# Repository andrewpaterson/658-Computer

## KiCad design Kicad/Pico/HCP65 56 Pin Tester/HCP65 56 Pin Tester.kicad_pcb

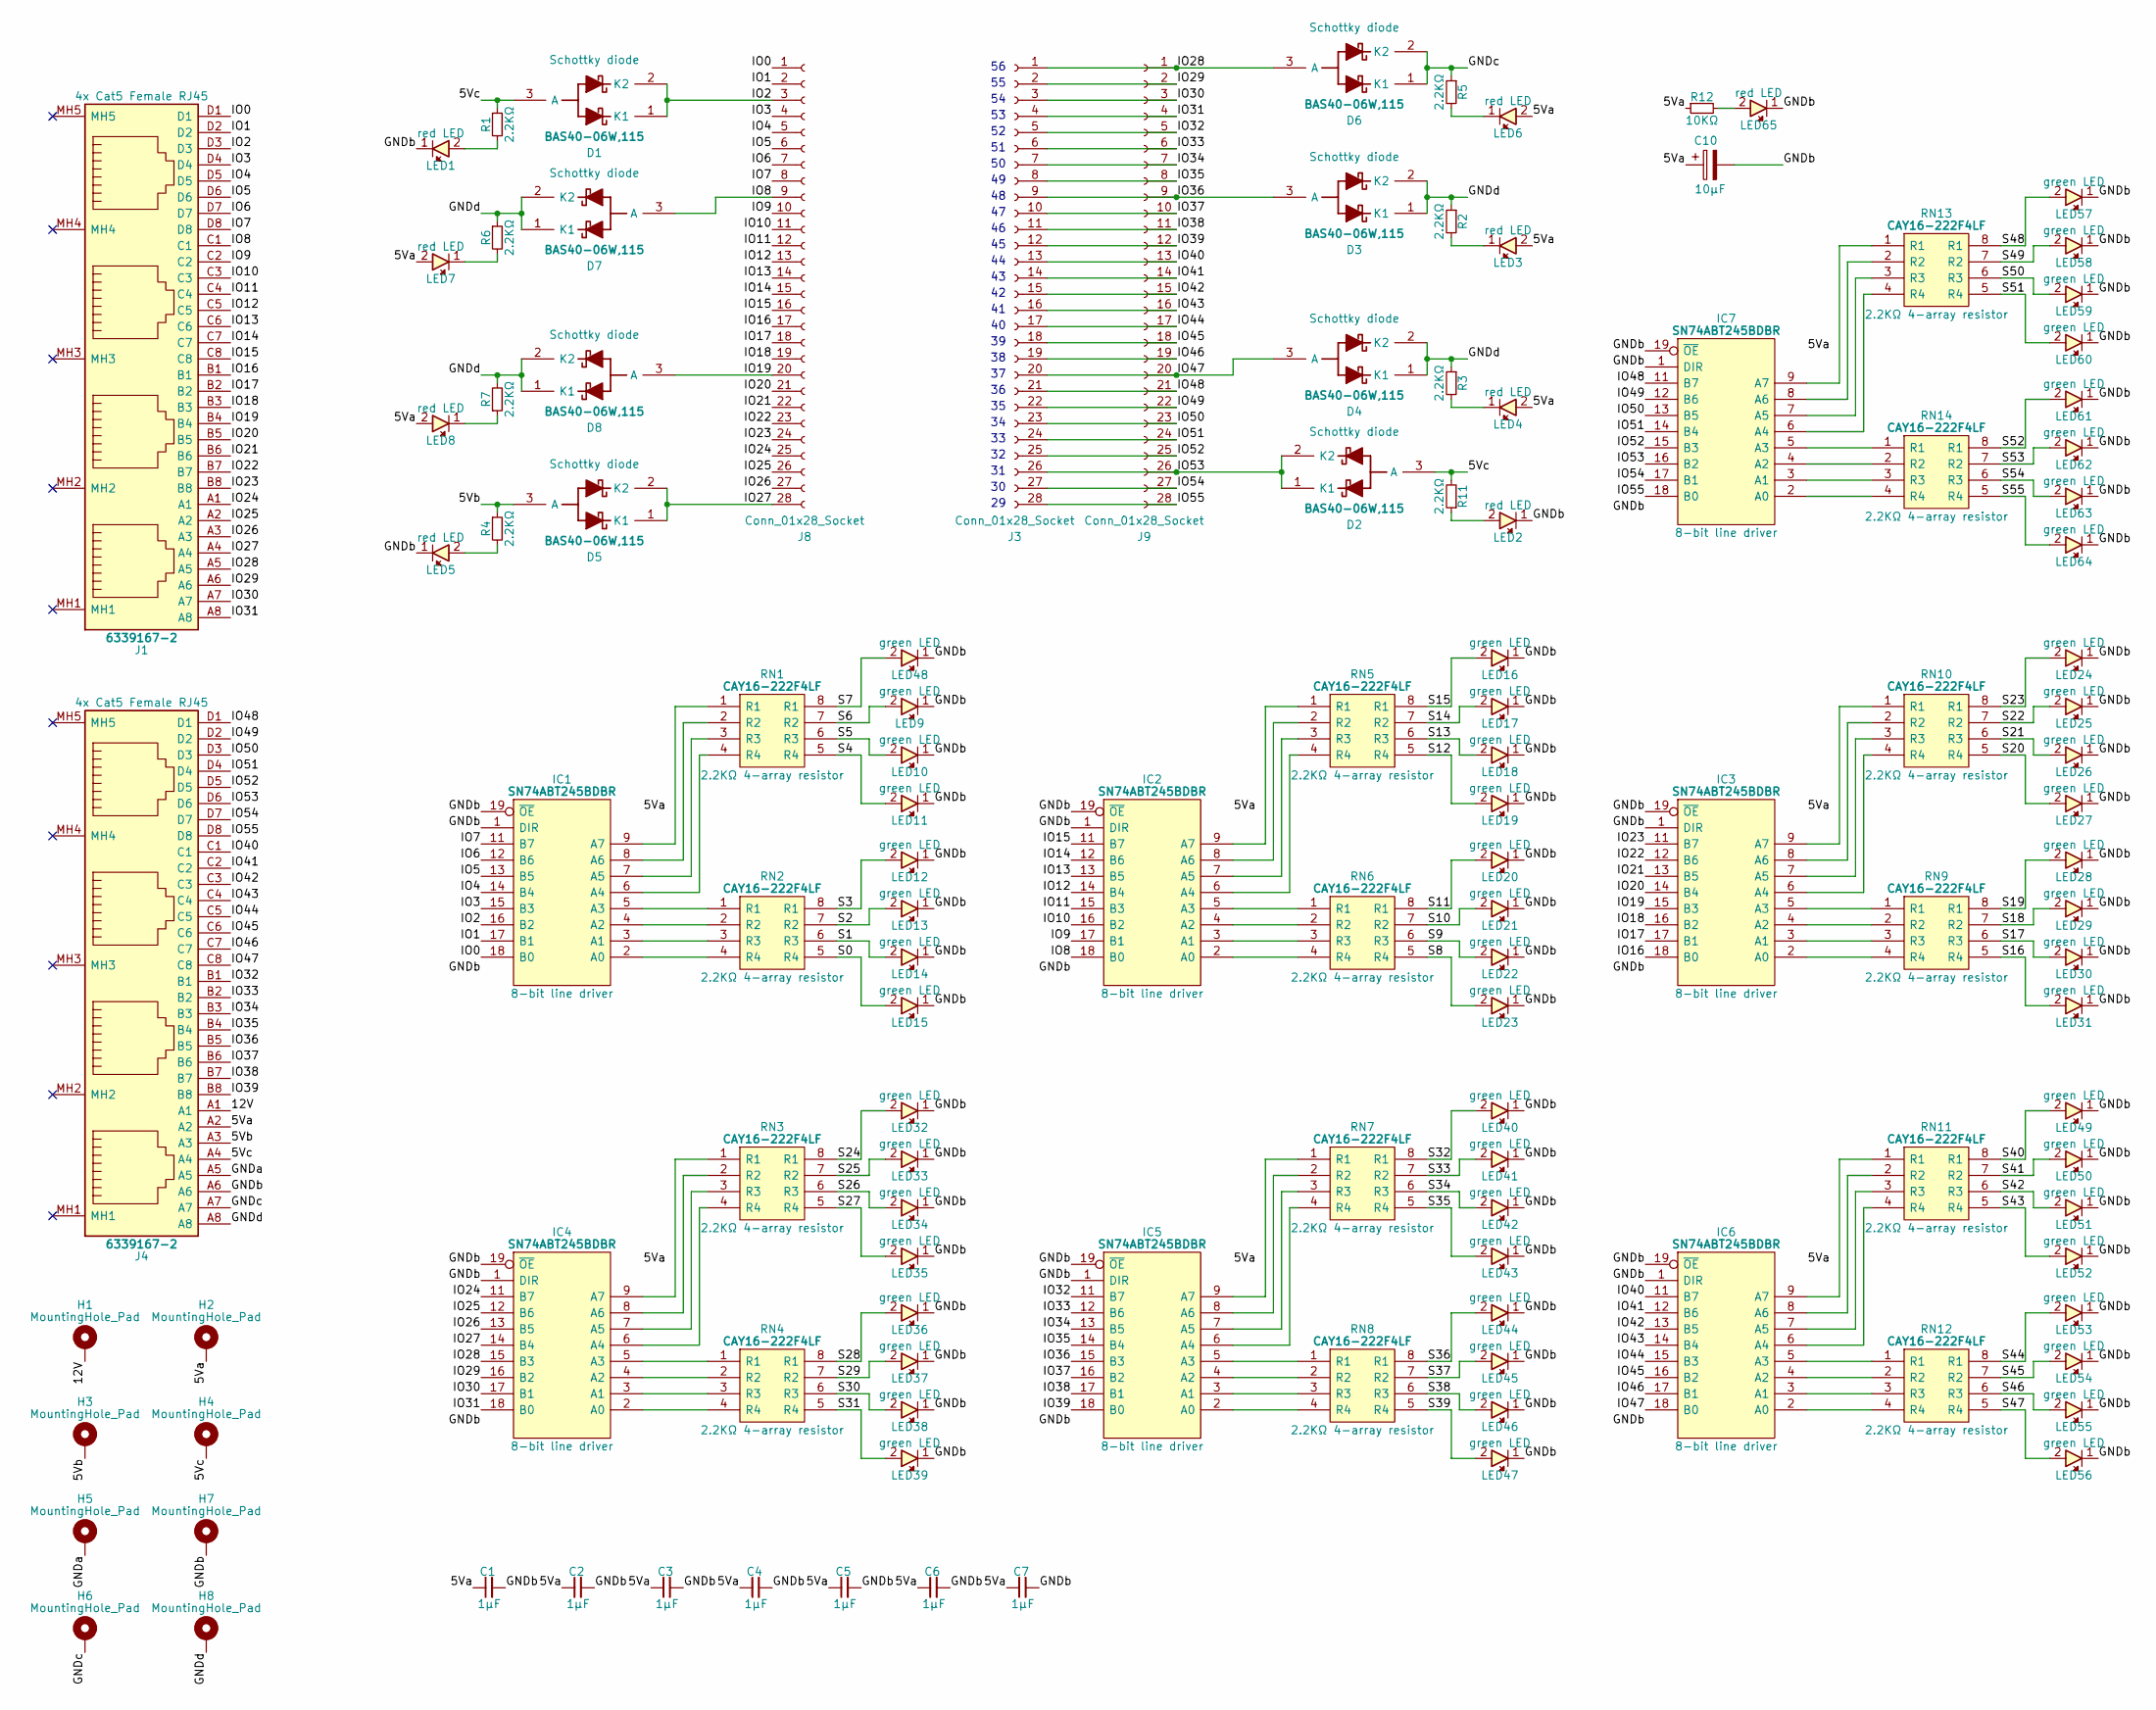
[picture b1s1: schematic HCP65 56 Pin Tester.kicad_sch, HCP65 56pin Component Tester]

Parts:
C1, C2, C3, C4, C5, C6, C7: 1μF; C_0805
C10: 10μF; CP_Radial_D4.0mm_P2.00mm
D1, D2, D3, D4, D5, D6, D7, D8: BAS40-06W,115; SOT65P210X110-3N; Manufacturer_Part_Number BAS40-06W,115; Mouser Part Number 771-BAS40-06W115
H1, H2, H3, H4, H5, H6, H7, H8: MountingHole_Pad; MountingHole_3.2mm_M3_Pad
IC1, IC2, IC3, IC4, IC5, IC6, IC7: SN74ABT245BDBR; SOP65P780X200-20N; Manufacturer_Part_Number SN74ABT245BDBR; Mouser Part Number 595-SN74ABT245BDBR
J1, J4: 6339167-2; 63391672; Manufacturer_Part_Number 6339167-2; Mouser Part Number 571-6339167-2
J3, J8, J9: Conn_01x28_Socket; PinSocket_1x28_P2.54mm_Vertical
LED1, LED2, LED3, LED4, LED5, LED6, LED7, LED8, LED65: 150224SS73100; 150224SS73100A; Manufacturer_Part_Number 150224SS73100; Mouser Part Number 710-150224SS73100
LED9, LED10, LED11, LED12, LED13, LED14, LED15, LED16, LED17, LED18, LED19, LED20, LED21, LED22, LED23, LED24, LED25, LED26, LED27, LED28, LED29, LED30, LED31, LED32, LED33, LED34, LED35, LED36, LED37, LED38, LED39, LED40, LED41, LED42, LED43, LED44, LED45, LED46, LED47, LED48, LED49, LED50, LED51, LED52, LED53, LED54, LED55, LED56, LED57, LED58, LED59, LED60, LED61, LED62, LED63, LED64: 150224VS73100A; Manufacturer_Part_Number 150224VS73100A; Mouser Part Number 710-150224VS73100A
R1, R2, R3, R4, R5, R6, R7, R11: 2.2KΩ; R_0805
R12: 10KΩ; R_0805
RN1, RN2, RN3, RN4, RN5, RN6, RN7, RN8, RN9, RN10, RN11, RN12, RN13, RN14: CAY16-222F4LF; CAY16-J4; Manufacturer_Part_Number CAY16-222F4LF; Mouser Part Number 652-CAY16-2201F4LF

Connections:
/5Va: C1.1, C2.1, C3.1, C4.1, C5.1, C6.1, C7.1, C10.1, H2.1, IC1.20 (5V), IC2.20 (5V), IC3.20 (5V), IC4.20 (5V), IC5.20 (5V), IC6.20 (5V), IC7.20 (5V), J4.A2, LED3.2, LED4.2, LED6.2, LED7.2, LED8.2, R12.1
/5Vb: D5.3 (A), H3.1, J4.A3, R4.1
/5Vc: D1.3 (A), D2.3 (A), H4.1, J4.A4, R1.1, R11.2
/12V: H1.1, J4.A1
/GNDa: H5.1, J4.A5
/GNDb: C1.2, C2.2, C3.2, C4.2, C5.2, C6.2, C7.2, C10.2, H7.1, IC1.1 (DIR), IC1.10 (GND), IC1.19 (~OE), IC2.1 (DIR), IC2.10 (GND), IC2.19 (~OE), IC3.1 (DIR), IC3.10 (GND), IC3.19 (~OE), IC4.1 (DIR), IC4.10 (GND), IC4.19 (~OE), IC5.1 (DIR), IC5.10 (GND), IC5.19 (~OE), IC6.1 (DIR), IC6.10 (GND), IC6.19 (~OE), IC7.1 (DIR), IC7.10 (GND), IC7.19 (~OE), J4.A6, LED1.1, LED2.1, LED5.1, LED9.1, LED10.1, LED11.1, LED12.1, LED13.1, LED14.1, LED15.1, LED16.1, LED17.1, LED18.1, LED19.1, LED20.1, LED21.1, LED22.1, LED23.1, LED24.1, LED25.1, LED26.1, LED27.1, LED28.1, LED29.1, LED30.1, LED31.1, LED32.1, LED33.1, LED34.1, LED35.1, LED36.1, LED37.1, LED38.1, LED39.1, LED40.1, LED41.1, LED42.1, LED43.1, LED44.1, LED45.1, LED46.1, LED47.1, LED48.1, LED49.1, LED50.1, LED51.1, LED52.1, LED53.1, LED54.1, LED55.1, LED56.1, LED57.1, LED58.1, LED59.1, LED60.1, LED61.1, LED62.1, LED63.1, LED64.1, LED65.1
/GNDc: D6.1 (K1), D6.2 (K2), H6.1, J4.A7, R5.1
/GNDd: D3.1 (K1), D3.2 (K2), D4.1 (K1), D4.2 (K2), D7.1 (K1), D7.2 (K2), D8.1 (K1), D8.2 (K2), H8.1, J4.A8, R2.1, R3.1, R6.1, R7.2
/IO0: IC1.18 (B0), J1.D1, J8.1
/IO1: IC1.17 (B1), J1.D2, J8.2
/IO2: D1.1 (K1), D1.2 (K2), IC1.16 (B2), J1.D3, J8.3
/IO3: IC1.15 (B3), J1.D4, J8.4
/IO4: IC1.14 (B4), J1.D5, J8.5
/IO5: IC1.13 (B5), J1.D6, J8.6
/IO6: IC1.12 (B6), J1.D7, J8.7
/IO7: IC1.11 (B7), J1.D8, J8.8
/IO8: D7.3 (A), IC2.18 (B0), J1.C1, J8.9
/IO9: IC2.17 (B1), J1.C2, J8.10
/IO10: IC2.16 (B2), J1.C3, J8.11
/IO11: IC2.15 (B3), J1.C4, J8.12
/IO12: IC2.14 (B4), J1.C5, J8.13
/IO13: IC2.13 (B5), J1.C6, J8.14
/IO14: IC2.12 (B6), J1.C7, J8.15
/IO15: IC2.11 (B7), J1.C8, J8.16
/IO16: IC3.18 (B0), J1.B1, J8.17
/IO17: IC3.17 (B1), J1.B2, J8.18
/IO18: IC3.16 (B2), J1.B3, J8.19
/IO19: D8.3 (A), IC3.15 (B3), J1.B4, J8.20
/IO20: IC3.14 (B4), J1.B5, J8.21
/IO21: IC3.13 (B5), J1.B6, J8.22
/IO22: IC3.12 (B6), J1.B7, J8.23
/IO23: IC3.11 (B7), J1.B8, J8.24
/IO24: IC4.11 (B7), J1.A1, J8.25
/IO25: IC4.12 (B6), J1.A2, J8.26
/IO26: IC4.13 (B5), J1.A3, J8.27
/IO27: D5.1 (K1), D5.2 (K2), IC4.14 (B4), J1.A4, J8.28
/IO28: D6.3 (A), IC4.15 (B3), J1.A5, J3.1, J9.1
/IO29: IC4.16 (B2), J1.A6, J3.2, J9.2
/IO30: IC4.17 (B1), J1.A7, J3.3, J9.3
/IO31: IC4.18 (B0), J1.A8, J3.4, J9.4
/IO32: IC5.11 (B7), J3.5, J4.B1, J9.5
/IO33: IC5.12 (B6), J3.6, J4.B2, J9.6
/IO34: IC5.13 (B5), J3.7, J4.B3, J9.7
/IO35: IC5.14 (B4), J3.8, J4.B4, J9.8
/IO36: D3.3 (A), IC5.15 (B3), J3.9, J4.B5, J9.9
/IO37: IC5.16 (B2), J3.10, J4.B6, J9.10
/IO38: IC5.17 (B1), J3.11, J4.B7, J9.11
/IO39: IC5.18 (B0), J3.12, J4.B8, J9.12
/IO40: IC6.11 (B7), J3.13, J4.C1, J9.13
/IO41: IC6.12 (B6), J3.14, J4.C2, J9.14
/IO42: IC6.13 (B5), J3.15, J4.C3, J9.15
/IO43: IC6.14 (B4), J3.16, J4.C4, J9.16
/IO44: IC6.15 (B3), J3.17, J4.C5, J9.17
/IO45: IC6.16 (B2), J3.18, J4.C6, J9.18
/IO46: IC6.17 (B1), J3.19, J4.C7, J9.19
/IO47: D4.3 (A), IC6.18 (B0), J3.20, J4.C8, J9.20
/IO48: IC7.11 (B7), J3.21, J4.D1, J9.21
/IO49: IC7.12 (B6), J3.22, J4.D2, J9.22
/IO50: IC7.13 (B5), J3.23, J4.D3, J9.23
/IO51: IC7.14 (B4), J3.24, J4.D4, J9.24
/IO52: IC7.15 (B3), J3.25, J4.D5, J9.25
/IO53: D2.1 (K1), D2.2 (K2), IC7.16 (B2), J3.26, J4.D6, J9.26
/IO54: IC7.17 (B1), J3.27, J4.D7, J9.27
/IO55: IC7.18 (B0), J3.28, J4.D8, J9.28
/S0: LED15.2, RN2.5 (R4)
/S1: LED14.2, RN2.6 (R3)
/S2: LED13.2, RN2.7 (R2)
/S3: LED12.2, RN2.8 (R1)
/S4: LED11.2, RN1.5 (R4)
/S5: LED10.2, RN1.6 (R3)
/S6: LED9.2, RN1.7 (R2)
/S7: LED48.2, RN1.8 (R1)
/S8: LED23.2, RN6.5 (R4)
/S9: LED22.2, RN6.6 (R3)
/S10: LED21.2, RN6.7 (R2)
/S11: LED20.2, RN6.8 (R1)
/S12: LED19.2, RN5.5 (R4)
/S13: LED18.2, RN5.6 (R3)
/S14: LED17.2, RN5.7 (R2)
/S15: LED16.2, RN5.8 (R1)
/S16: LED31.2, RN9.5 (R4)
/S17: LED30.2, RN9.6 (R3)
/S18: LED29.2, RN9.7 (R2)
/S19: LED28.2, RN9.8 (R1)
/S20: LED27.2, RN10.5 (R4)
/S21: LED26.2, RN10.6 (R3)
/S22: LED25.2, RN10.7 (R2)
/S23: LED24.2, RN10.8 (R1)
/S24: LED32.2, RN3.8 (R1)
/S25: LED33.2, RN3.7 (R2)
/S26: LED34.2, RN3.6 (R3)
/S27: LED35.2, RN3.5 (R4)
/S28: LED36.2, RN4.8 (R1)
/S29: LED37.2, RN4.7 (R2)
/S30: LED38.2, RN4.6 (R3)
/S31: LED39.2, RN4.5 (R4)
/S32: LED40.2, RN7.8 (R1)
/S33: LED41.2, RN7.7 (R2)
/S34: LED42.2, RN7.6 (R3)
/S35: LED43.2, RN7.5 (R4)
/S36: LED44.2, RN8.8 (R1)
/S37: LED45.2, RN8.7 (R2)
/S38: LED46.2, RN8.6 (R3)
/S39: LED47.2, RN8.5 (R4)
/S40: LED49.2, RN11.8 (R1)
/S41: LED50.2, RN11.7 (R2)
/S42: LED51.2, RN11.6 (R3)
/S43: LED52.2, RN11.5 (R4)
/S44: LED53.2, RN12.8 (R1)
/S45: LED54.2, RN12.7 (R2)
/S46: LED55.2, RN12.6 (R3)
/S47: LED56.2, RN12.5 (R4)
/S48: LED57.2, RN13.8 (R1)
/S49: LED58.2, RN13.7 (R2)
/S50: LED59.2, RN13.6 (R3)
/S51: LED60.2, RN13.5 (R4)
/S52: LED61.2, RN14.8 (R1)
/S53: LED62.2, RN14.7 (R2)
/S54: LED63.2, RN14.6 (R3)
/S55: LED64.2, RN14.5 (R4)
unnamed: IC1.2 (A0), RN2.4 (R4)
unnamed: IC1.3 (A1), RN2.3 (R3)
unnamed: IC1.4 (A2), RN2.2 (R2)
unnamed: IC1.5 (A3), RN2.1 (R1)
unnamed: IC1.6 (A4), RN1.4 (R4)
unnamed: IC1.7 (A5), RN1.3 (R3)
unnamed: IC1.8 (A6), RN1.2 (R2)
unnamed: IC1.9 (A7), RN1.1 (R1)
unnamed: IC2.2 (A0), RN6.4 (R4)
unnamed: IC2.3 (A1), RN6.3 (R3)
unnamed: IC2.4 (A2), RN6.2 (R2)
unnamed: IC2.5 (A3), RN6.1 (R1)
unnamed: IC2.6 (A4), RN5.4 (R4)
unnamed: IC2.7 (A5), RN5.3 (R3)
unnamed: IC2.8 (A6), RN5.2 (R2)
unnamed: IC2.9 (A7), RN5.1 (R1)
unnamed: IC3.2 (A0), RN9.4 (R4)
unnamed: IC3.3 (A1), RN9.3 (R3)
unnamed: IC3.4 (A2), RN9.2 (R2)
unnamed: IC3.5 (A3), RN9.1 (R1)
unnamed: IC3.6 (A4), RN10.4 (R4)
unnamed: IC3.7 (A5), RN10.3 (R3)
unnamed: IC3.8 (A6), RN10.2 (R2)
unnamed: IC3.9 (A7), RN10.1 (R1)
unnamed: IC4.2 (A0), RN4.4 (R4)
unnamed: IC4.3 (A1), RN4.3 (R3)
unnamed: IC4.4 (A2), RN4.2 (R2)
unnamed: IC4.5 (A3), RN4.1 (R1)
unnamed: IC4.6 (A4), RN3.4 (R4)
unnamed: IC4.7 (A5), RN3.3 (R3)
unnamed: IC4.8 (A6), RN3.2 (R2)
unnamed: IC4.9 (A7), RN3.1 (R1)
unnamed: IC5.2 (A0), RN8.4 (R4)
unnamed: IC5.3 (A1), RN8.3 (R3)
unnamed: IC5.4 (A2), RN8.2 (R2)
unnamed: IC5.5 (A3), RN8.1 (R1)
unnamed: IC5.6 (A4), RN7.4 (R4)
unnamed: IC5.7 (A5), RN7.3 (R3)
unnamed: IC5.8 (A6), RN7.2 (R2)
unnamed: IC5.9 (A7), RN7.1 (R1)
unnamed: IC6.2 (A0), RN12.4 (R4)
unnamed: IC6.3 (A1), RN12.3 (R3)
unnamed: IC6.4 (A2), RN12.2 (R2)
unnamed: IC6.5 (A3), RN12.1 (R1)
unnamed: IC6.6 (A4), RN11.4 (R4)
unnamed: IC6.7 (A5), RN11.3 (R3)
unnamed: IC6.8 (A6), RN11.2 (R2)
unnamed: IC6.9 (A7), RN11.1 (R1)
unnamed: IC7.2 (A0), RN14.4 (R4)
unnamed: IC7.3 (A1), RN14.3 (R3)
unnamed: IC7.4 (A2), RN14.2 (R2)
unnamed: IC7.5 (A3), RN14.1 (R1)
unnamed: IC7.6 (A4), RN13.4 (R4)
unnamed: IC7.7 (A5), RN13.3 (R3)
unnamed: IC7.8 (A6), RN13.2 (R2)
unnamed: IC7.9 (A7), RN13.1 (R1)
unnamed: LED1.2, R1.2
unnamed: LED2.2, R11.1
unnamed: LED3.1, R2.2
unnamed: LED4.1, R3.2
unnamed: LED5.2, R4.2
unnamed: LED6.1, R5.2
unnamed: LED7.1, R6.2
unnamed: LED8.1, R7.1
unnamed: LED65.2, R12.2

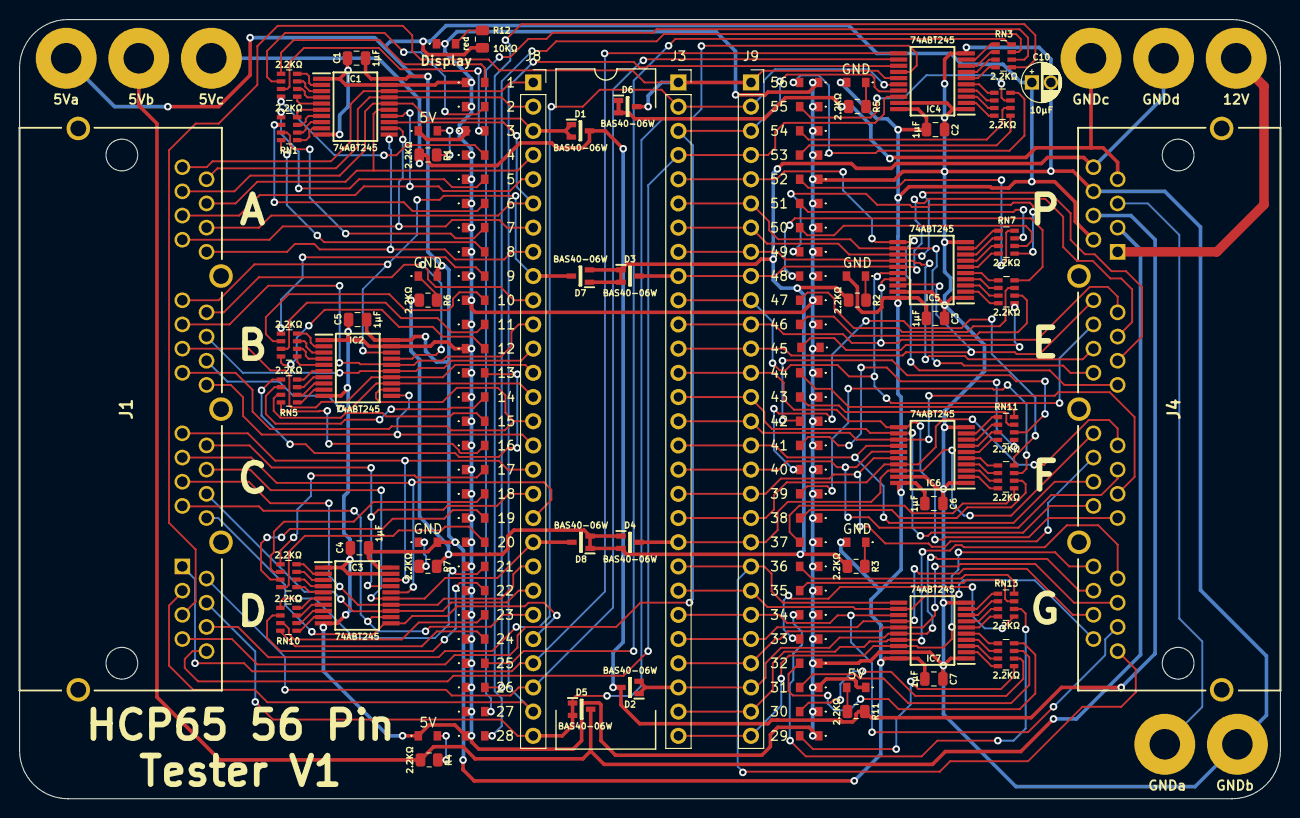
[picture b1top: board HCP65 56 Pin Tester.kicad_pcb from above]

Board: 2 copper layers, 132.4 x 81.8 mm, 124 parts (0 on the bottom side), 185 nets.

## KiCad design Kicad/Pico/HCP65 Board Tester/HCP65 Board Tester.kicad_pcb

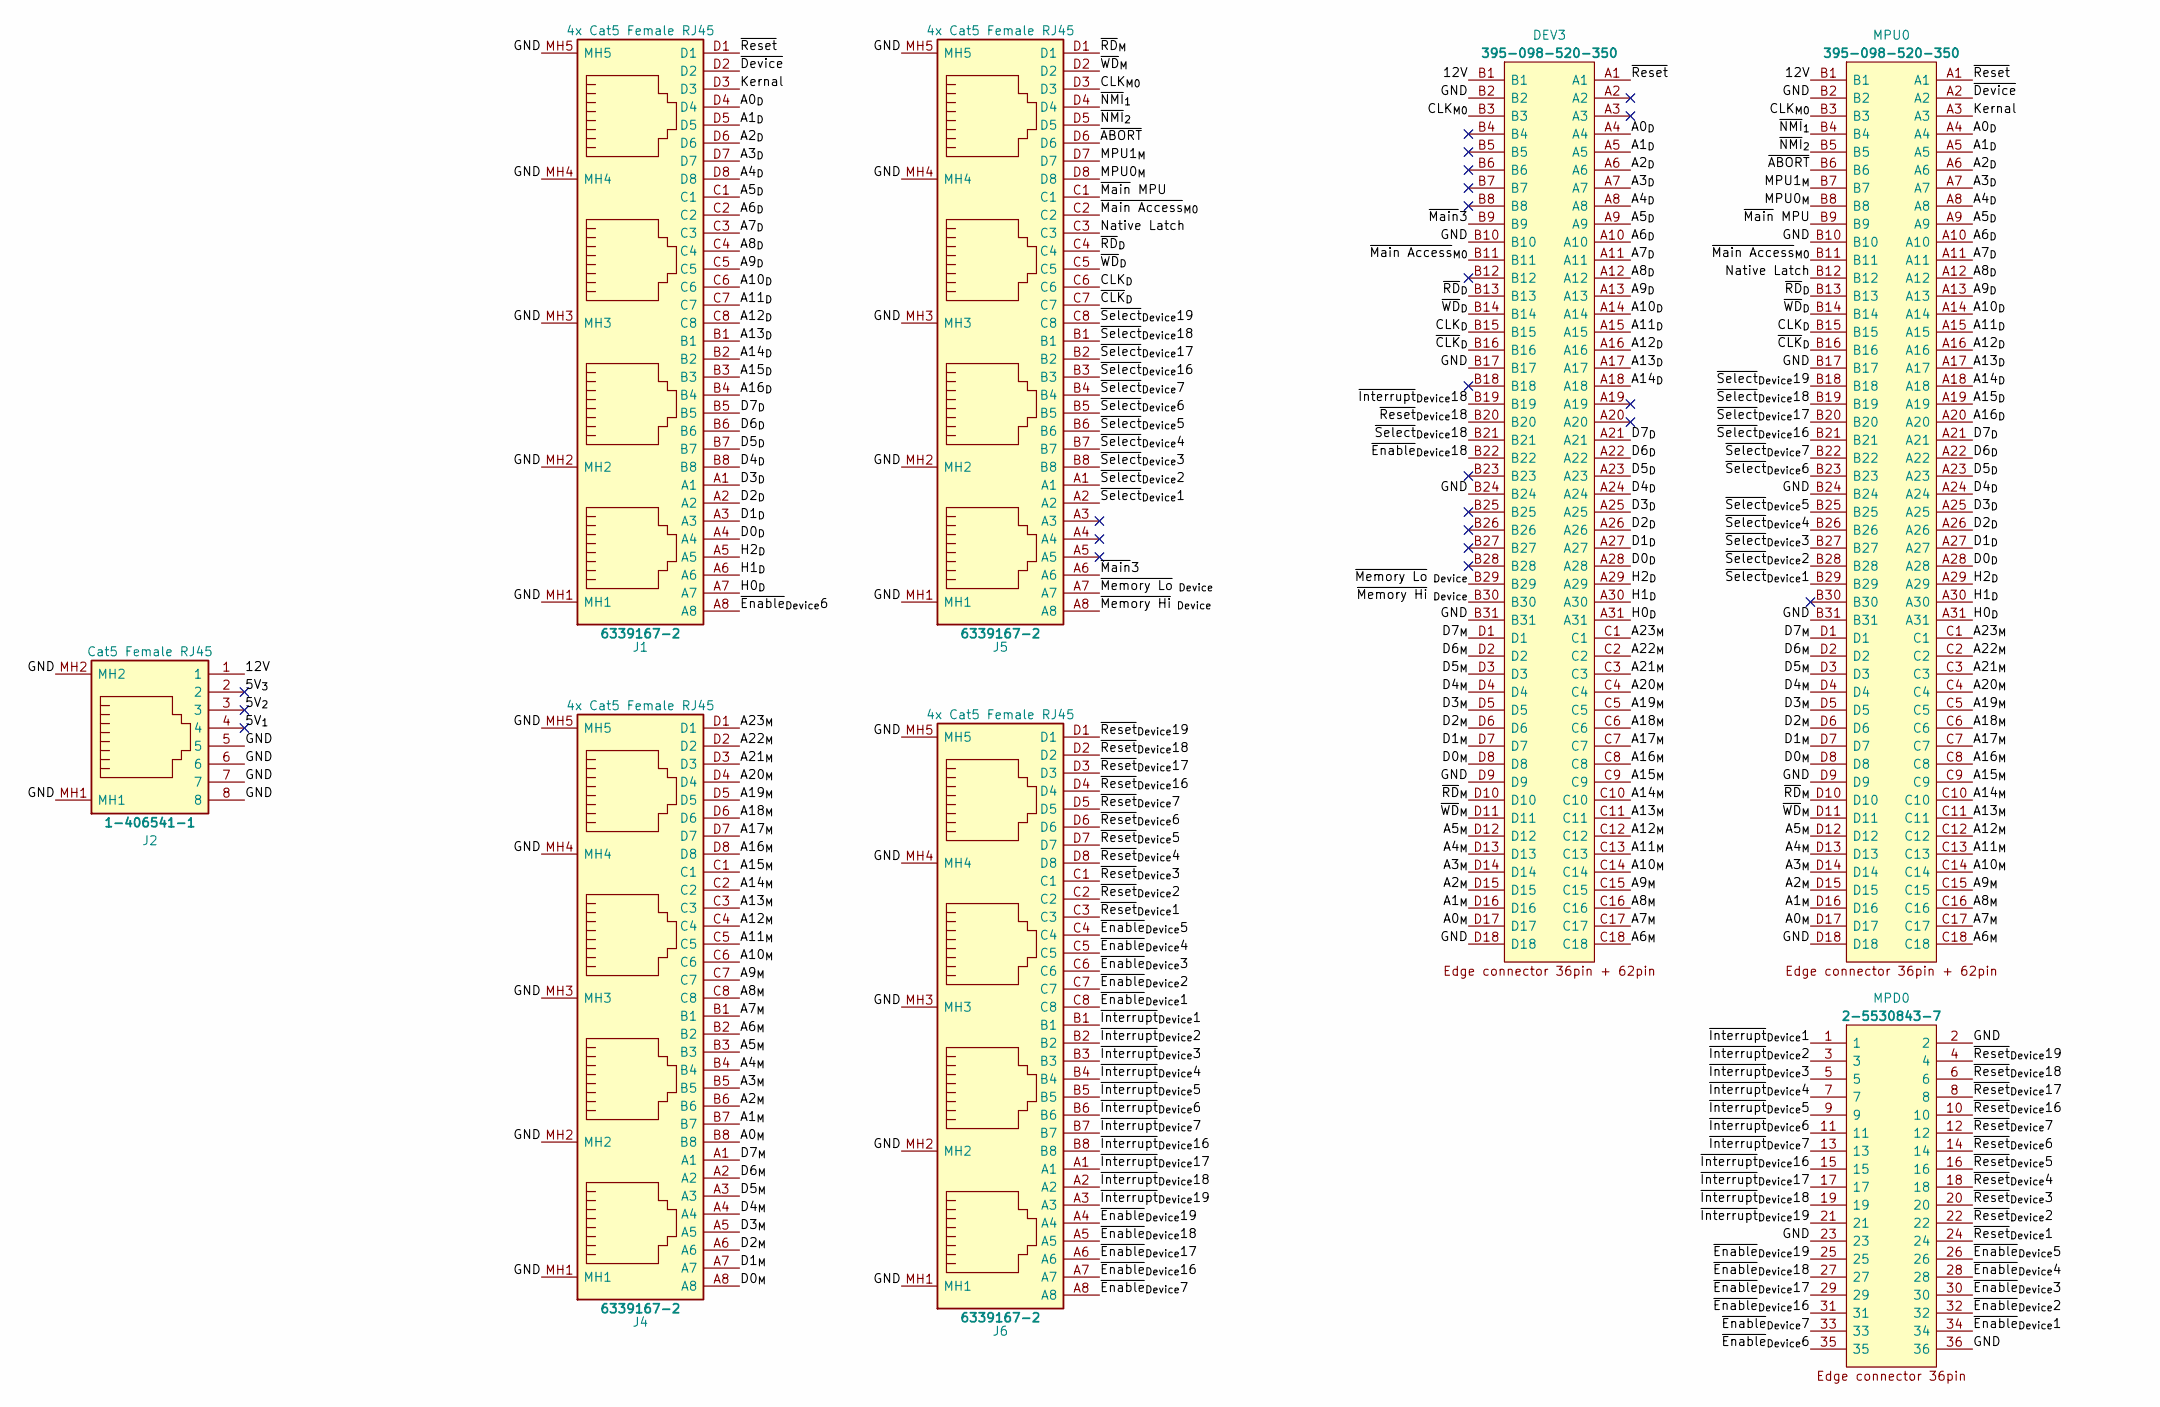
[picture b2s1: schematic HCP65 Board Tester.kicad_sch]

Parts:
DEV3: 395-098-520-350; 395098520350; Manufacturer_Part_Number 395-098-520-350; Mouser Part Number 587-395-098-520-350
J1, J4, J5, J6: 6339167-2; 63391672; Manufacturer_Part_Number 6339167-2; Mouser Part Number 571-6339167-2
J2: 1-406541-1; 1-406541-1_1; Manufacturer_Part_Number 1-406541-1; Mouser Part Number 571-1-406541-1
MPD0: 2-5530843-7; 255308437; Manufacturer_Part_Number 2-5530843-7; Mouser Part Number 571-2-5530843-7
MPU0: 395-098-520-350; 395098520350; Manufacturer_Part_Number 395-098-520-350; Mouser Part Number 587-395-098-520-350

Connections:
/5V_{1}: J2.4
/5V_{2}: J2.3
/5V_{3}: J2.2
/12V: DEV3.B1, J2.1, MPU0.B1
/A0_{D}: DEV3.A4, J1.D4, MPU0.A4
/A0_{M}: DEV3.D17, J4.B8, MPU0.D17
/A1_{D}: DEV3.A5, J1.D5, MPU0.A5
/A1_{M}: DEV3.D16, J4.B7, MPU0.D16
/A2_{D}: DEV3.A6, J1.D6, MPU0.A6
/A2_{M}: DEV3.D15, J4.B6, MPU0.D15
/A3_{D}: DEV3.A7, J1.D7, MPU0.A7
/A3_{M}: DEV3.D14, J4.B5, MPU0.D14
/A4_{D}: DEV3.A8, J1.D8, MPU0.A8
/A4_{M}: DEV3.D13, J4.B4, MPU0.D13
/A5_{D}: DEV3.A9, J1.C1, MPU0.A9
/A5_{M}: DEV3.D12, J4.B3, MPU0.D12
/A6_{D}: DEV3.A10, J1.C2, MPU0.A10
/A6_{M}: DEV3.C18, J4.B2, MPU0.C18
/A7_{D}: DEV3.A11, J1.C3, MPU0.A11
/A7_{M}: DEV3.C17, J4.B1, MPU0.C17
/A8_{D}: DEV3.A12, J1.C4, MPU0.A12
/A8_{M}: DEV3.C16, J4.C8, MPU0.C16
/A9_{D}: DEV3.A13, J1.C5, MPU0.A13
/A9_{M}: DEV3.C15, J4.C7, MPU0.C15
/A10_{D}: DEV3.A14, J1.C6, MPU0.A14
/A10_{M}: DEV3.C14, J4.C6, MPU0.C14
/A11_{D}: DEV3.A15, J1.C7, MPU0.A15
/A11_{M}: DEV3.C13, J4.C5, MPU0.C13
/A12_{D}: DEV3.A16, J1.C8, MPU0.A16
/A12_{M}: DEV3.C12, J4.C4, MPU0.C12
/A13_{D}: DEV3.A17, J1.B1, MPU0.A17
/A13_{M}: DEV3.C11, J4.C3, MPU0.C11
/A14_{D}: DEV3.A18, J1.B2, MPU0.A18
/A14_{M}: DEV3.C10, J4.C2, MPU0.C10
/A15_{D}: J1.B3, MPU0.A19
/A15_{M}: DEV3.C9, J4.C1, MPU0.C9
/A16_{D}: J1.B4, MPU0.A20
/A16_{M}: DEV3.C8, J4.D8, MPU0.C8
/A17_{M}: DEV3.C7, J4.D7, MPU0.C7
/A18_{M}: DEV3.C6, J4.D6, MPU0.C6
/A19_{M}: DEV3.C5, J4.D5, MPU0.C5
/A20_{M}: DEV3.C4, J4.D4, MPU0.C4
/A21_{M}: DEV3.C3, J4.D3, MPU0.C3
/A22_{M}: DEV3.C2, J4.D2, MPU0.C2
/A23_{M}: DEV3.C1, J4.D1, MPU0.C1
/CLK_{D}: DEV3.B15, J5.C6, MPU0.B15
/CLK_{M0}: DEV3.B3, J5.D3, MPU0.B3
/D0_{D}: DEV3.A28, J1.A4, MPU0.A28
/D0_{M}: DEV3.D8, J4.A8, MPU0.D8
/D1_{D}: DEV3.A27, J1.A3, MPU0.A27
/D1_{M}: DEV3.D7, J4.A7, MPU0.D7
/D2_{D}: DEV3.A26, J1.A2, MPU0.A26
/D2_{M}: DEV3.D6, J4.A6, MPU0.D6
/D3_{D}: DEV3.A25, J1.A1, MPU0.A25
/D3_{M}: DEV3.D5, J4.A5, MPU0.D5
/D4_{D}: DEV3.A24, J1.B8, MPU0.A24
/D4_{M}: DEV3.D4, J4.A4, MPU0.D4
/D5_{D}: DEV3.A23, J1.B7, MPU0.A23
/D5_{M}: DEV3.D3, J4.A3, MPU0.D3
/D6_{D}: DEV3.A22, J1.B6, MPU0.A22
/D6_{M}: DEV3.D2, J4.A2, MPU0.D2
/D7_{D}: DEV3.A21, J1.B5, MPU0.A21
/D7_{M}: DEV3.D1, J4.A1, MPU0.D1
/GND: DEV3.B2, DEV3.B10, DEV3.B17, DEV3.B24, DEV3.B31, DEV3.D9, DEV3.D18, J1.MH1, J1.MH2, J1.MH3, J1.MH4, J1.MH5, J2.5, J2.6, J2.7, J2.8, J2.MH1, J2.MH2, J4.MH1, J4.MH2, J4.MH3, J4.MH4, J4.MH5, J5.MH1, J5.MH2, J5.MH3, J5.MH4, J5.MH5, J6.MH1, J6.MH2, J6.MH3, J6.MH4, J6.MH5, MPD0.2, MPD0.23, MPD0.36, MPU0.B2, MPU0.B10, MPU0.B17, MPU0.B24, MPU0.B31, MPU0.D9, MPU0.D18
/H0_{D}: DEV3.A31, J1.A7, MPU0.A31
/H1_{D}: DEV3.A30, J1.A6, MPU0.A30
/H2_{D}: DEV3.A29, J1.A5, MPU0.A29
/Kernal: J1.D3, MPU0.A3
/MPU0_{M}: J5.D8, MPU0.B8
/MPU1_{M}: J5.D7, MPU0.B7
/Native Latch: J5.C3, MPU0.B12
/~ABORT: J5.D6, MPU0.B6
/~CLK_{D}: DEV3.B16, J5.C7, MPU0.B16
/~Device: J1.D2, MPU0.A2
/~Enable_{Device}1: J6.C8, MPD0.34
/~Enable_{Device}2: J6.C7, MPD0.32
/~Enable_{Device}3: J6.C6, MPD0.30
/~Enable_{Device}4: J6.C5, MPD0.28
/~Enable_{Device}5: J6.C4, MPD0.26
/~Enable_{Device}6: J1.A8, MPD0.35
/~Enable_{Device}7: J6.A8, MPD0.33
/~Enable_{Device}16: J6.A7, MPD0.31
/~Enable_{Device}17: J6.A6, MPD0.29
/~Enable_{Device}18: DEV3.B22, J6.A5, MPD0.27
/~Enable_{Device}19: J6.A4, MPD0.25
/~Interrupt_{Device}1: J6.B1, MPD0.1
/~Interrupt_{Device}2: J6.B2, MPD0.3
/~Interrupt_{Device}3: J6.B3, MPD0.5
/~Interrupt_{Device}4: J6.B4, MPD0.7
/~Interrupt_{Device}5: J6.B5, MPD0.9
/~Interrupt_{Device}6: J6.B6, MPD0.11
/~Interrupt_{Device}7: J6.B7, MPD0.13
/~Interrupt_{Device}16: J6.B8, MPD0.15
/~Interrupt_{Device}17: J6.A1, MPD0.17
/~Interrupt_{Device}18: DEV3.B19, J6.A2, MPD0.19
/~Interrupt_{Device}19: J6.A3, MPD0.21
/~Main Access_{M0}: DEV3.B11, J5.C2, MPU0.B11
/~Main3: DEV3.B9, J5.A6
/~Main MPU: J5.C1, MPU0.B9
/~Memory Hi_{ Device}: DEV3.B30, J5.A8
/~Memory Lo_{ Device}: DEV3.B29, J5.A7
/~NMI_{1}: J5.D4, MPU0.B4
/~NMI_{2}: J5.D5, MPU0.B5
/~RD_{D}: DEV3.B13, J5.C4, MPU0.B13
/~RD_{M}: DEV3.D10, J5.D1, MPU0.D10
/~Reset: DEV3.A1, J1.D1, MPU0.A1
/~Reset_{Device}1: J6.C3, MPD0.24
/~Reset_{Device}2: J6.C2, MPD0.22
/~Reset_{Device}3: J6.C1, MPD0.20
/~Reset_{Device}4: J6.D8, MPD0.18
/~Reset_{Device}5: J6.D7, MPD0.16
/~Reset_{Device}6: J6.D6, MPD0.14
/~Reset_{Device}7: J6.D5, MPD0.12
/~Reset_{Device}16: J6.D4, MPD0.10
/~Reset_{Device}17: J6.D3, MPD0.8
/~Reset_{Device}18: DEV3.B20, J6.D2, MPD0.6
/~Reset_{Device}19: J6.D1, MPD0.4
/~Select_{Device}1: J5.A2, MPU0.B29
/~Select_{Device}2: J5.A1, MPU0.B28
/~Select_{Device}3: J5.B8, MPU0.B27
/~Select_{Device}4: J5.B7, MPU0.B26
/~Select_{Device}5: J5.B6, MPU0.B25
/~Select_{Device}6: J5.B5, MPU0.B23
/~Select_{Device}7: J5.B4, MPU0.B22
/~Select_{Device}16: J5.B3, MPU0.B21
/~Select_{Device}17: J5.B2, MPU0.B20
/~Select_{Device}18: DEV3.B21, J5.B1, MPU0.B19
/~Select_{Device}19: J5.C8, MPU0.B18
/~WD_{D}: DEV3.B14, J5.C5, MPU0.B14
/~WD_{M}: DEV3.D11, J5.D2, MPU0.D11

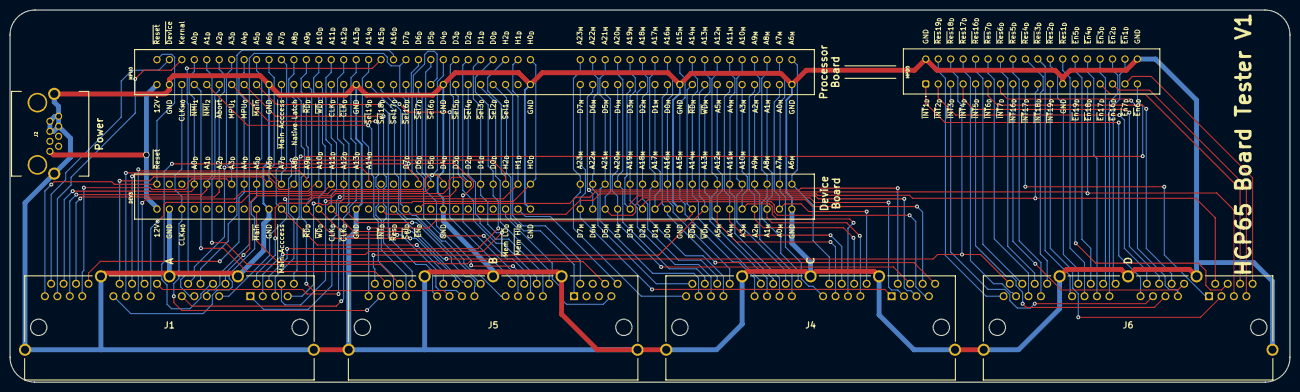
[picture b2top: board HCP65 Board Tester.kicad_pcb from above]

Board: 2 copper layers, 261.1 x 75.9 mm, 8 parts (0 on the bottom side), 127 nets.

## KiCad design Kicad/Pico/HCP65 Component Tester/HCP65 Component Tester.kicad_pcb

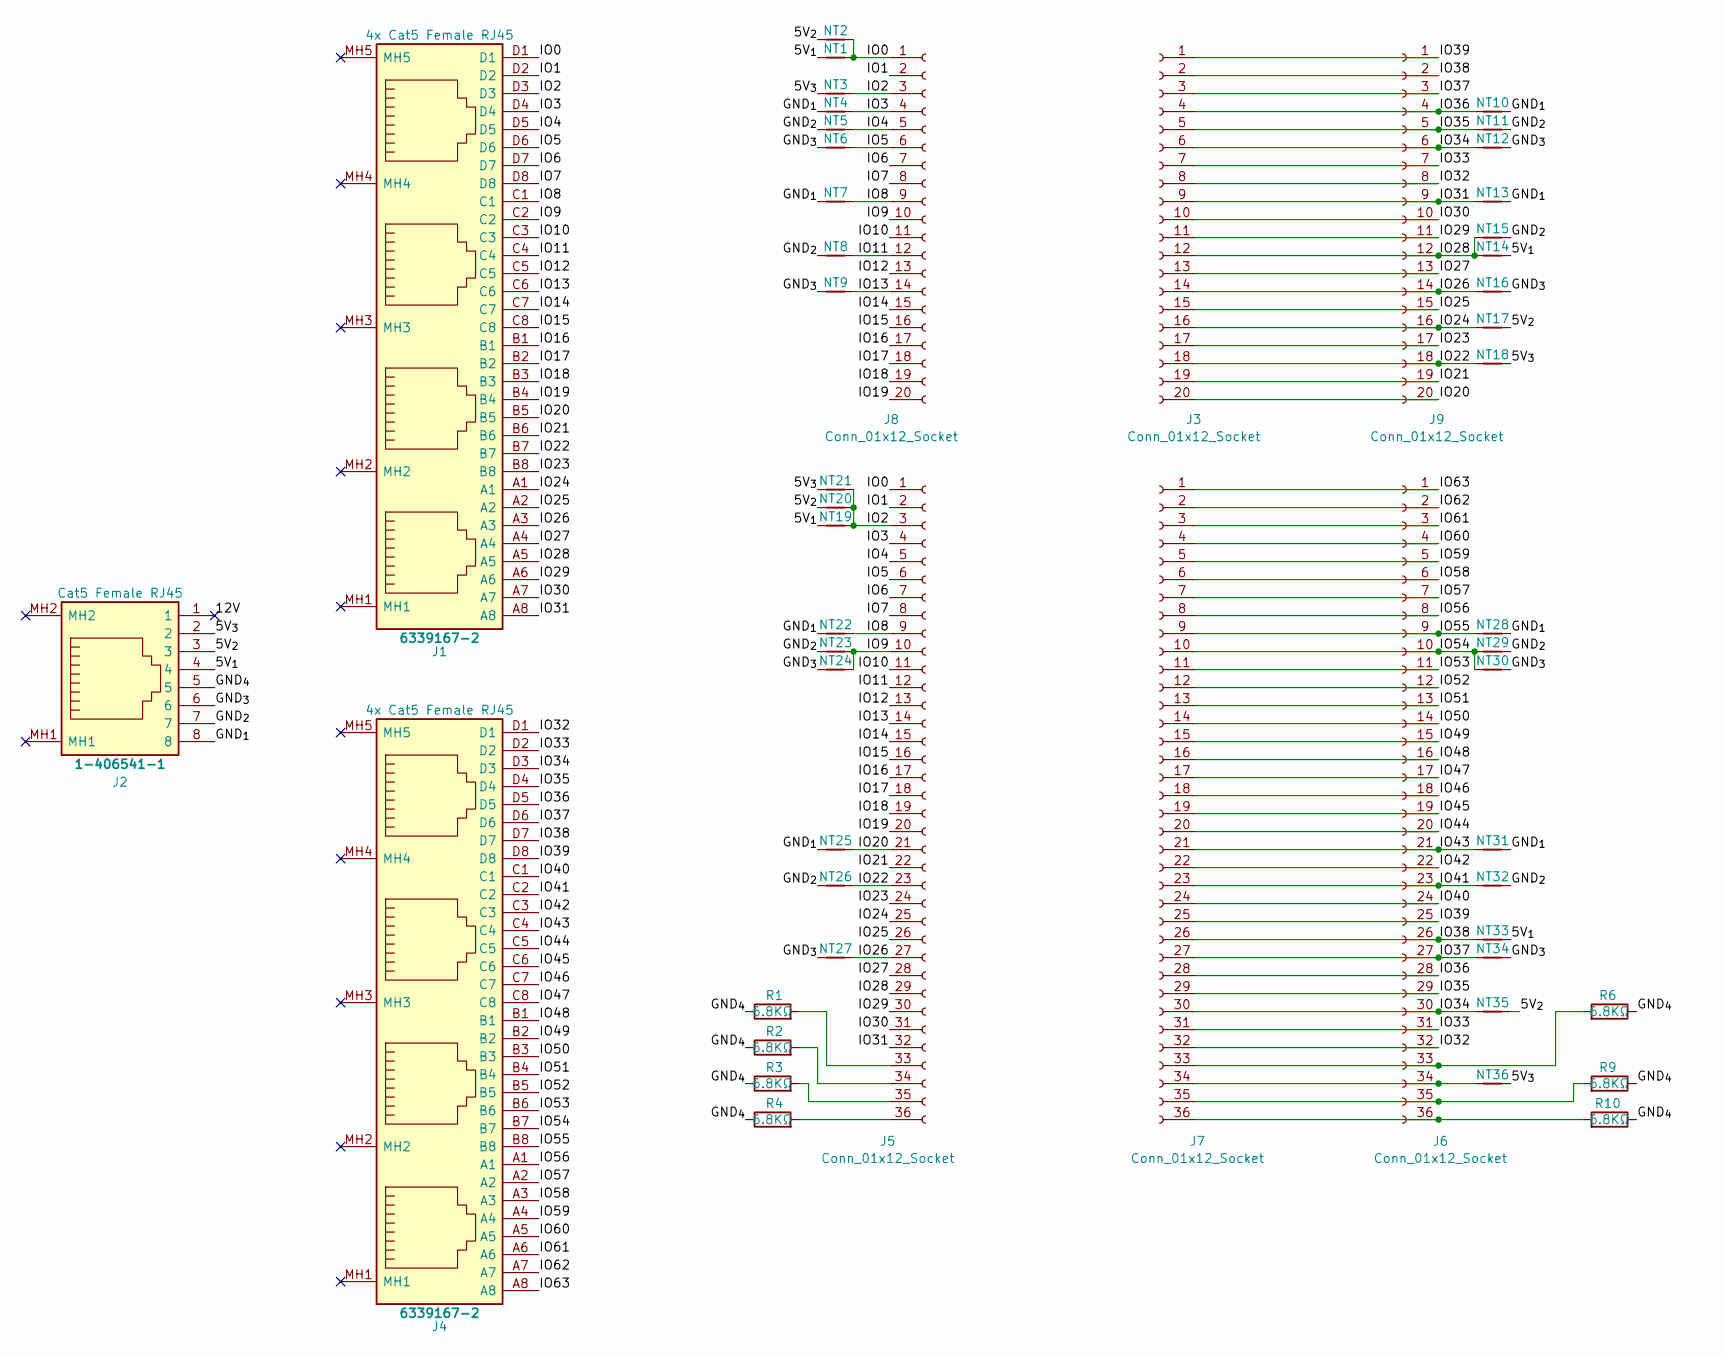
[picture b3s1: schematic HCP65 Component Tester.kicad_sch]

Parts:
J1, J4: 6339167-2; 63391672; Manufacturer_Part_Number 6339167-2; Mouser Part Number 571-6339167-2
J2: 1-406541-1; 1-406541-1_1; Manufacturer_Part_Number 1-406541-1; Mouser Part Number 571-1-406541-1
J3, J8, J9: Conn_01x12_Socket; PinSocket_1x20_P2.54mm_Vertical
J5, J6, J7: Conn_01x12_Socket; PinSocket_1x36_P2.54mm_Vertical
NT1, NT2, NT3, NT4, NT5, NT6, NT7, NT8, NT9, NT10, NT11, NT12, NT13, NT14, NT15, NT16, NT17, NT18, NT19, NT20, NT21, NT22, NT23, NT24, NT25, NT26, NT27, NT28, NT29, NT30, NT31, NT32, NT33, NT34, NT35, NT36: NetTie_2; NetTie-2_SMD_Pad0.5mm
R1, R2, R3, R4, R6, R9, R10: 6.8KΩ; R_Axial_DIN0207_L6.3mm_D2.5mm_P7.62mm_Horizontal

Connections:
/5V_{1}: J2.4, NT1.1, NT14.2, NT19.1, NT33.2
/5V_{2}: J2.3, NT2.1, NT17.2, NT20.1, NT35.2
/5V_{3}: J2.2, NT3.1, NT18.2, NT21.1, NT36.2
/12V: J2.1
/GND_{1}: J2.8, NT4.1, NT7.1, NT10.2, NT13.2, NT22.1, NT25.1, NT28.2, NT31.2
/GND_{2}: J2.7, NT5.1, NT8.1, NT11.2, NT15.2, NT23.1, NT26.1, NT29.2, NT32.2
/GND_{3}: J2.6, NT6.1, NT9.1, NT12.2, NT16.2, NT24.1, NT27.1, NT30.2, NT34.2
/GND_{4}: J2.5, R1.1, R2.1, R3.1, R4.1, R6.1, R9.1, R10.1
/IO0: J1.D1, J5.1, J8.1, NT1.2, NT2.2
/IO1: J1.D2, J5.2, J8.2
/IO2: J1.D3, J5.3, J8.3, NT3.2, NT19.2, NT20.2, NT21.2
/IO3: J1.D4, J5.4, J8.4, NT4.2
/IO4: J1.D5, J5.5, J8.5, NT5.2
/IO5: J1.D6, J5.6, J8.6, NT6.2
/IO6: J1.D7, J5.7, J8.7
/IO7: J1.D8, J5.8, J8.8
/IO8: J1.C1, J5.9, J8.9, NT7.2, NT22.2
/IO9: J1.C2, J5.10, J8.10, NT23.2, NT24.2
/IO10: J1.C3, J5.11, J8.11
/IO11: J1.C4, J5.12, J8.12, NT8.2
/IO12: J1.C5, J5.13, J8.13
/IO13: J1.C6, J5.14, J8.14, NT9.2
/IO14: J1.C7, J5.15, J8.15
/IO15: J1.C8, J5.16, J8.16
/IO16: J1.B1, J5.17, J8.17
/IO17: J1.B2, J5.18, J8.18
/IO18: J1.B3, J5.19, J8.19
/IO19: J1.B4, J5.20, J8.20
/IO20: J1.B5, J3.20, J5.21, J9.20, NT25.2
/IO21: J1.B6, J3.19, J5.22, J9.19
/IO22: J1.B7, J3.18, J5.23, J9.18, NT18.1, NT26.2
/IO23: J1.B8, J3.17, J5.24, J9.17
/IO24: J1.A1, J3.16, J5.25, J9.16, NT17.1
/IO25: J1.A2, J3.15, J5.26, J9.15
/IO26: J1.A3, J3.14, J5.27, J9.14, NT16.1, NT27.2
/IO27: J1.A4, J3.13, J5.28, J9.13
/IO28: J1.A5, J3.12, J5.29, J9.12, NT14.1, NT15.1
/IO29: J1.A6, J3.11, J5.30, J9.11
/IO30: J1.A7, J3.10, J5.31, J9.10
/IO31: J1.A8, J3.9, J5.32, J9.9, NT13.1
/IO32: J3.8, J4.D1, J6.32, J7.32, J9.8
/IO33: J3.7, J4.D2, J6.31, J7.31, J9.7
/IO34: J3.6, J4.D3, J6.30, J7.30, J9.6, NT12.1, NT35.1
/IO35: J3.5, J4.D4, J6.29, J7.29, J9.5, NT11.1
/IO36: J3.4, J4.D5, J6.28, J7.28, J9.4, NT10.1
/IO37: J3.3, J4.D6, J6.27, J7.27, J9.3, NT34.1
/IO38: J3.2, J4.D7, J6.26, J7.26, J9.2, NT33.1
/IO39: J3.1, J4.D8, J6.25, J7.25, J9.1
/IO40: J4.C1, J6.24, J7.24
/IO41: J4.C2, J6.23, J7.23, NT32.1
/IO42: J4.C3, J6.22, J7.22
/IO43: J4.C4, J6.21, J7.21, NT31.1
/IO44: J4.C5, J6.20, J7.20
/IO45: J4.C6, J6.19, J7.19
/IO46: J4.C7, J6.18, J7.18
/IO47: J4.C8, J6.17, J7.17
/IO48: J4.B1, J6.16, J7.16
/IO49: J4.B2, J6.15, J7.15
/IO50: J4.B3, J6.14, J7.14
/IO51: J4.B4, J6.13, J7.13
/IO52: J4.B5, J6.12, J7.12
/IO53: J4.B6, J6.11, J7.11
/IO54: J4.B7, J6.10, J7.10, NT29.1, NT30.1
/IO55: J4.B8, J6.9, J7.9, NT28.1
/IO56: J4.A1, J6.8, J7.8
/IO57: J4.A2, J6.7, J7.7
/IO58: J4.A3, J6.6, J7.6
/IO59: J4.A4, J6.5, J7.5
/IO60: J4.A5, J6.4, J7.4
/IO61: J4.A6, J6.3, J7.3
/IO62: J4.A7, J6.2, J7.2
/IO63: J4.A8, J6.1, J7.1
unnamed: J5.33, R1.2
unnamed: J5.34, R2.2
unnamed: J5.35, R3.2
unnamed: J5.36, R4.2
unnamed: J6.33, J7.33, R6.2
unnamed: J6.34, J7.34, NT36.1
unnamed: J6.35, J7.35, R9.2
unnamed: J6.36, J7.36, R10.2

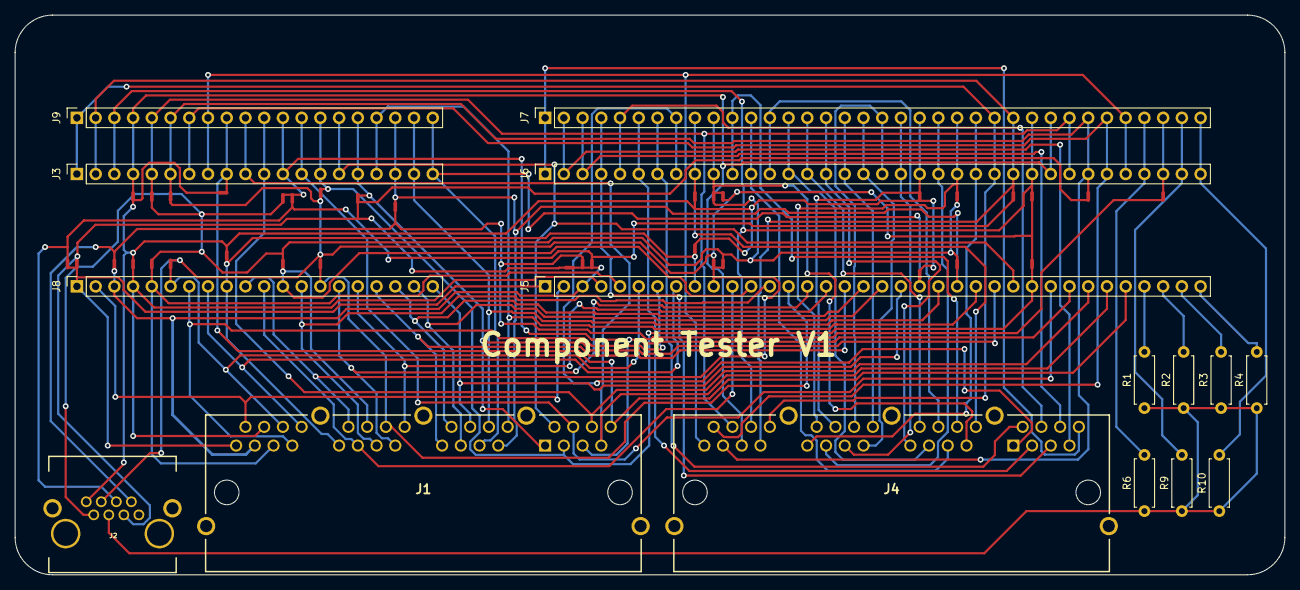
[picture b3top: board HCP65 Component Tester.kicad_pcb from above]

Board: 2 copper layers, 172.2 x 75.9 mm, 52 parts (0 on the bottom side), 79 nets.
